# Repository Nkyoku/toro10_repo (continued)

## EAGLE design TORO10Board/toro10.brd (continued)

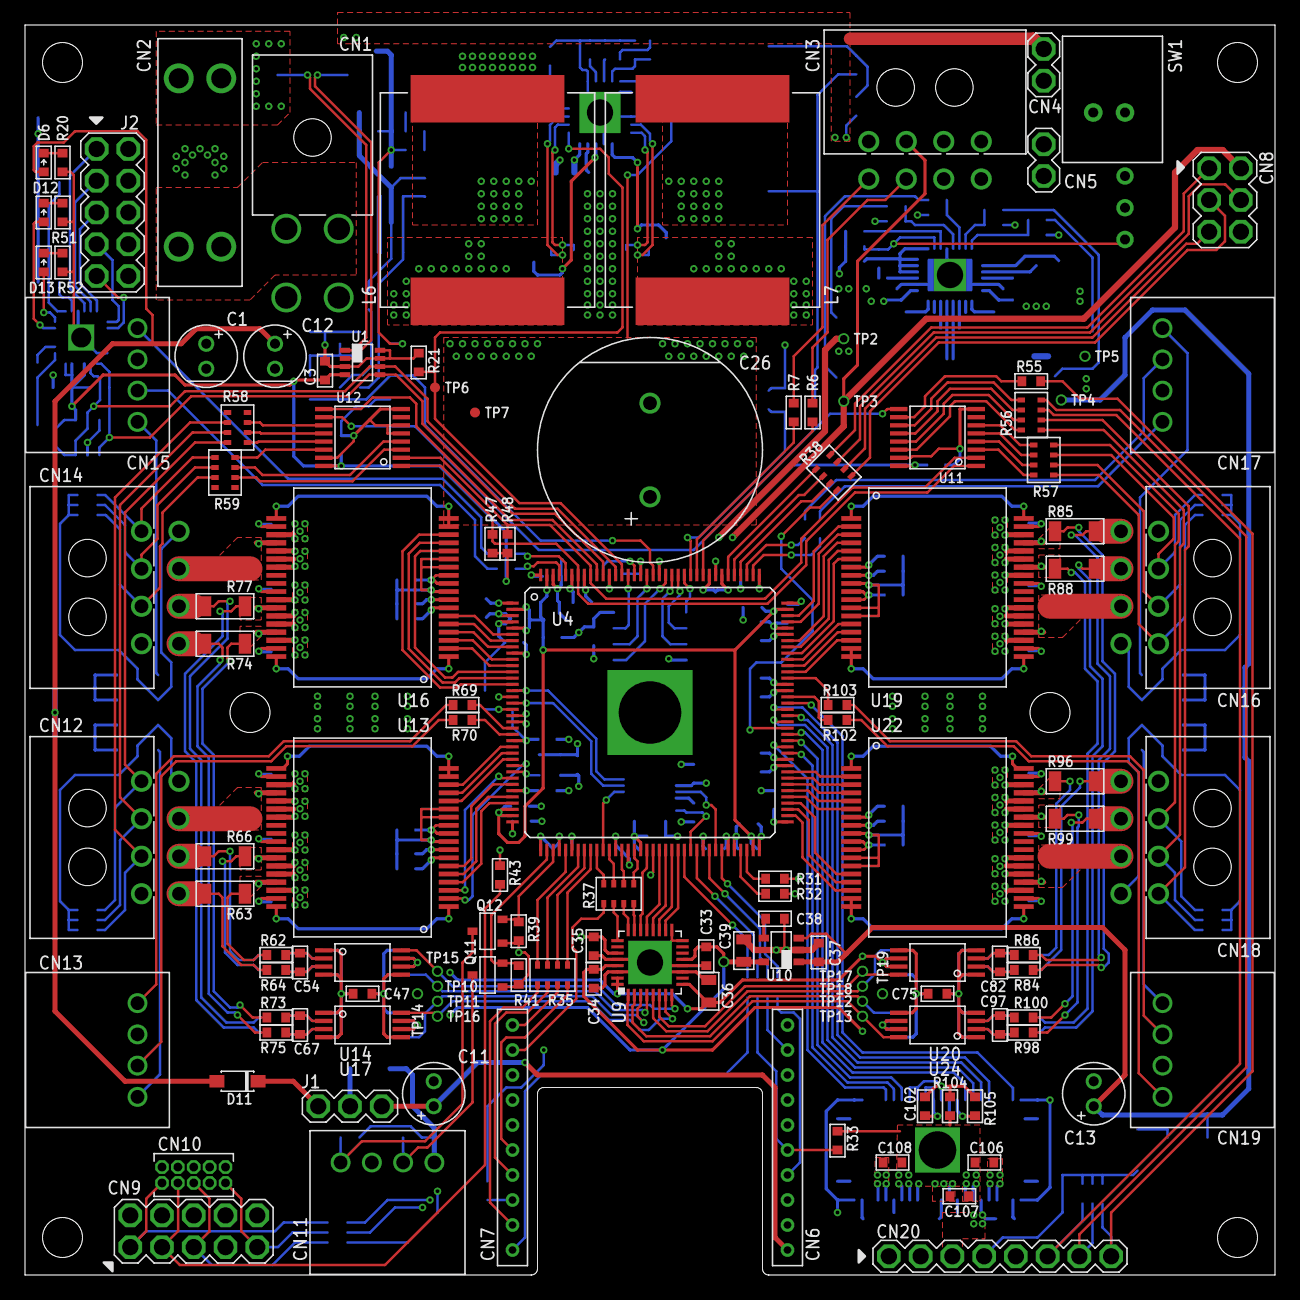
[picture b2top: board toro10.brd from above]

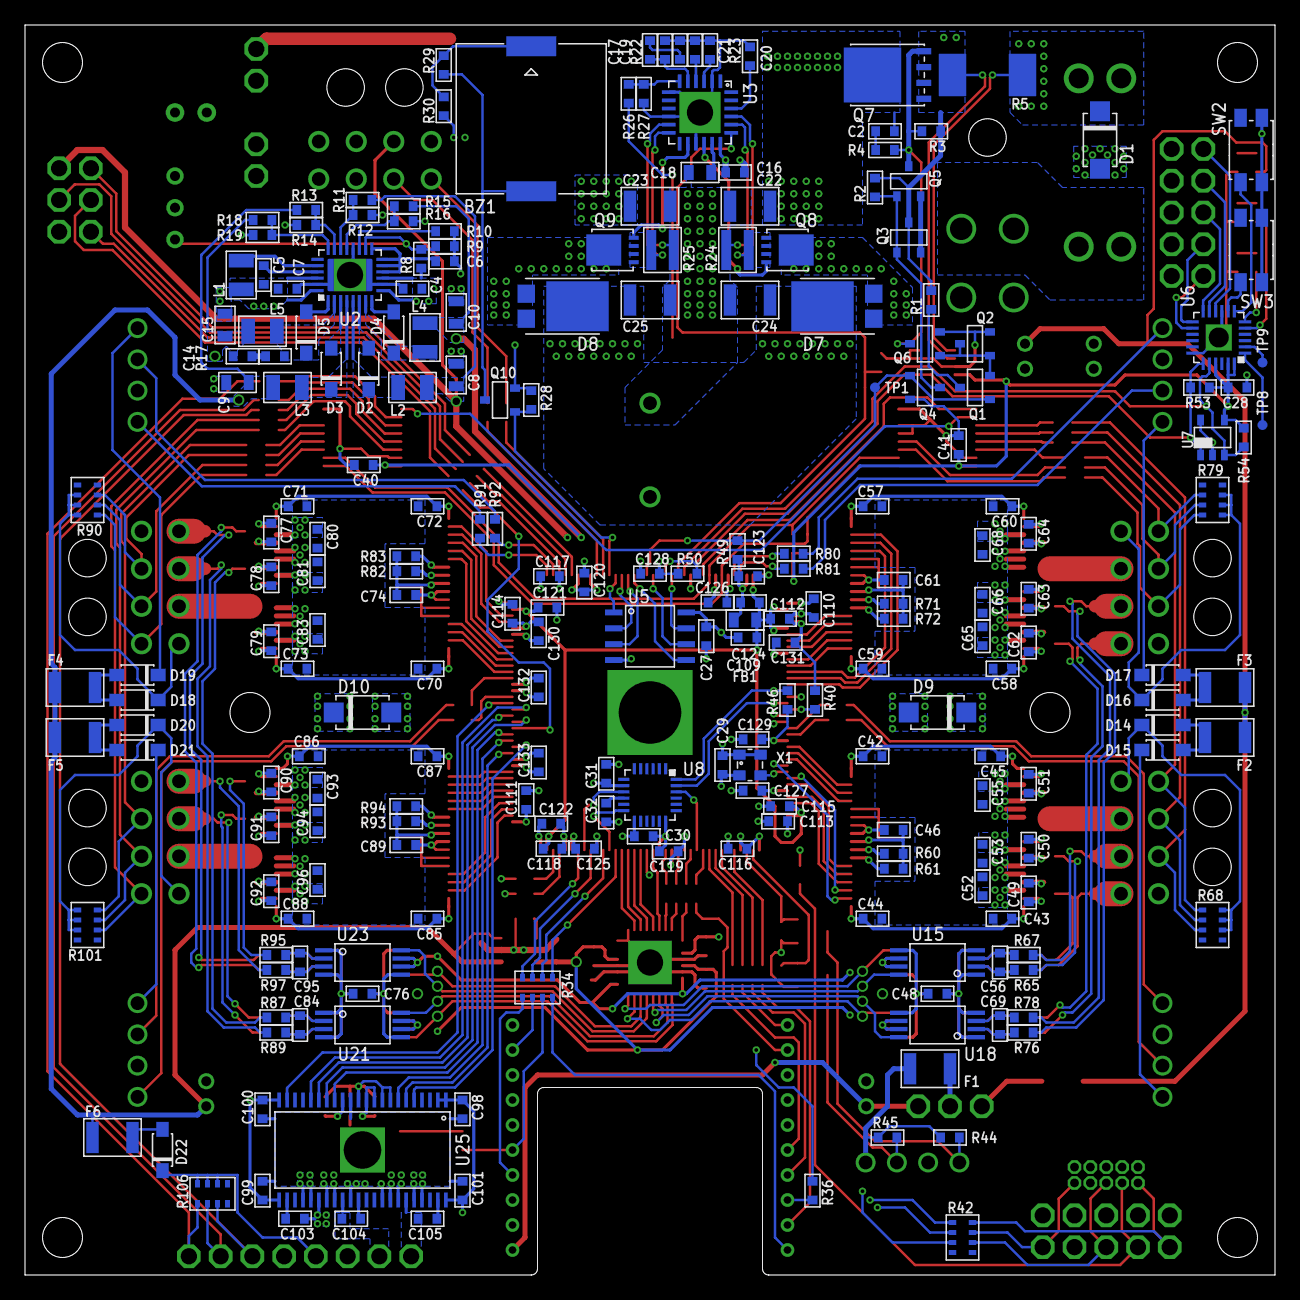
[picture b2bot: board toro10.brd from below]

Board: 4 copper layers, 100.0 x 100.0 mm, 358 parts (230 on the bottom side), 329 nets.

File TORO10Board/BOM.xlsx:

Device | Model Number | Value | Package | Qty | Parts
Resistor |  | 0Ω | 1608 | 16 | R62, R64, R65, R67, R73, R75, R76, R78, R84, R86, R87, R89, R95, R97, R98, R100
Resistor | WSLF25121L000FEA | 1mΩ | WSLF2512 | 1 | R5
Resistor |  | 2mΩ | 3216 | 8 | R63, R66, R74, R77, R85, R88, R96, R99
Resistor | PRL1632-R005-F-T1 | 5mΩ | 3216WL | 2 | R24, R25
Resistor |  | 1Ω | 1608 | 5 | R60, R71, R82, R93, R104
Resistor |  | 51Ω | 1608 | 6 | R6, R7, R31, R32, R36, R43
Resistor |  | 1kΩ | 1608 | 14 | R4, R17, R29, R30, R51, R52, R69, R70, R80, R81, R91, R92, R102, R103
Resistor |  | 2.2kΩ | 1608 | 7 | R21, R33, R44, R45, R49, R53, R54
Resistor |  | 3.3kΩ | 1608 | 1 | R19
Resistor |  | 4.7kΩ | 1608 | 5 | R20, R27, R28, R39, R41
Resistor |  | 10kΩ | 1608 | 8 | R2, R10, R40, R46, R47, R48, R50, R55
Resistor |  | 15kΩ | 1608 | 1 | R12
Resistor |  | 22kΩ | 1608 | 6 | R9, R14, R61, R72, R83, R94
Resistor |  | 33kΩ | 1608 | 1 | R23
Resistor |  | 47kΩ | 1608 | 4 | R11, R16, R18, R105
Resistor |  | 68.1kΩ | 1608 | 1 | R22
Resistor |  | 130kΩ | 1608 | 2 | R13, R15
Resistor |  | 180kΩ | 1608 | 1 | R26
Resistor |  | 220kΩ | 1608 | 2 | R1, R3
Resistor |  | 270kΩ | 1608 | 1 | R8
Resistor Array |  | 51Ωx4 | 3216 | 5 | R34, R35, R37, R38, R42
Resistor Array |  | 1kΩx4 | 3216 | 4 | R56, R57, R58, R59
Resistor Array |  | 100kΩx4 | 3216 | 5 | R68, R79, R90, R101, R106
Ceramic Capacitor |  | Do Not Mount | 1608 | 8 | C54, C56, C67, C69, C82, C84, C95, C97
Ceramic Capacitor |  | 100pF | 1608 | 1 | C19
Ceramic Capacitor |  | 1nF | 1608 | 2 | C14, C20
Ceramic Capacitor |  | 10nF | 1608 | 3 | C17, C29, C38
Ceramic Capacitor |  | 100nF 63V | 1608 | 72 | C2, C3, C6, C21, C27, C28, C31, C40, C41, C46, C47, C48, C49, C50, C51, C52, C5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
Ceramic Capacitor |  | 1uF 63V | 1608 | 30 | C4, C5, C7, C16, C30, C32, C33, C34, C35, C37, C42, C43, C44, C45, C57, C58, C5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
Ceramic Capacitor | GRM21BB31E106KA | 10uF 16V | 2012 | 7 | C8, ,C9, C10, C15, C18, C39, C109
Ceramic Capacitor | GRM32ER7YA106KA12 | 10uF 35V | 3225 | 2 | C22, C23
Ceramic Capacitor | GRM32ER71J106MA12L | 10uF 63V | 3225 | 2 | C24, C25
Ceramic Capacitor | GRM21BR61E226ME44 | 22uF 6.3V | 2012 | 1 | C36
Aluminum Capacitor | 35PK47MEFC5X11 | 47uF 35V | φ5mm | 1 | C1
Aluminum Capacitor | 25PK100MEFC5X11 | 100uF 16V | φ5mm | 3 | C11, C12, C13
Aluminum Capacitor | UPW1J391MHD6 | 390uF 63V | φ18mm | 1 | C26
Inductor | MAMK2520T4R7M | 4.7uH | 2520 | 5 | L1, L2, L3, L4, L5
Inductor | IHLP6767GZER8R2M11 | 8.2uH | 17.15mm x 17.15mm | 2 | L6, L7
Ferrite Bead | BLM18PG471SN1D |  | 1608 | 1 | FB1
Polyswitch | MICROSMD010F-02 |  | 3225 | 6 | F1, F2, F3, F4, F5, F6
Silicon Diode | GS1010FL |  | SOD123 | 10 | D11, D14, D15, D16, D17, D18, D19, D20, D21, D22
Schottky Diode | SS2040FL |  | SOD123 | 4 | D2, D3, D4, D5
Schottky Diode | FSV2060L |  | TO-277-3 | 2 | D7, D8
TVS Diode | SMAJ26A |  | DO-214AC | 1 | D1
TVS Diode | SMAJ48A |  | DO-214AC | 2 | D9, D10
LED |  | Green | 1608 | 1 | D12
LED |  | Orange | 1608 | 1 | D6
LED |  | Red | 1608 | 1 | D13
NPN Transistor | 2SC2712-GR |  | SOT23-3 | 2 | Q2, Q6
Nch MOSFET | BSS138 |  | SOT23-3 | 7 | Q1, Q3, Q4, Q5, Q10, Q11, Q12
Nch MOSFET | TPN7R506NH,L1Q |  | TSON-8_3.3 | 2 | Q8, Q9
Pch MOSFET | SI7135DP-T1-GE3 |  | POWERPAK-SO-8-S | 1 | Q7
LDO Regulator | SPX3819M5-L-5-0/TR |  | SOT23-5 | 1 | U10
Buck Regulator | LT3504EUFD#PBF |  | QFN28-0.5 | 1 | U2
Boost Regulator | LTC3862EUH-1#PBF |  | QFN24-0.65 | 1 | U3
Serializer | SN74LV165APWRG3 |  | TSSOP16 | 2 | U11, U12
A/D Conveter | ADS7223SRHBT |  | QFN32-0.5 | 1 | U9
Oscillator | ASDMB-30.000MHZ-LC-T |  | 2520 | 1 | X1
EEPROM | 24AA02E48T-I/OT |  | SOT23-5 | 1 | U7
Flash Memory | IS25LP016D-JNLE |  | SOP8 | 1 | U5
I/O Expander | PCAL6416AHF,128 |  | QFN24-0.5 | 1 | U6
Motor Driver | DRV8312DDWR |  | HTSSOP44 | 1 | U25
Motor Driver | DRV8332DKDR |  | HSSOP36 | 4 | U13, U16, U19, U22
Inertial Measurement Unit | ICM-20689 |  | QFN24 | 1 | U8
Current Sense Amplifier | INA219AIDCNR |  | SOT23-8 | 1 | U1
Current Sense Amplifier | INA240A2PWR |  | TSSOP8 | 8 | U14, U15, U17, U18, U20, U21, U23, U24
FPGA | 10M16SCE144C8G |  | QFP144 | 1 | U4
Piezoelectric Sounder | PKLCS1212E4001-R1 |  | PKLCS1212 | 1 | BZ1
Toggle Switch | B-12JV |  | B-12JV | 1 | SW1
Tactile Switch | EVQ-PUB02K |  | EVQ-PU_BK | 2 | SW2, SW3
Header | 3557-20 |  | 3557 | 1 | CN2
Header | 0430450801 |  | 43045-0800 | 5 | CN3, CN12, CN14, CN16, CN18
Header | 0534260410 |  | 53426-04 | 5 | CN11, CN13, CN15, CN17, CN19
Header | 0039301040 |  | 5569-04A2 | 1 | CN1
Pin Header | Pin Header 1x2 2.54mm Pitch |  | PIN1X2 | 2 | CN4, CN5
Pin Header | Pin Header 1x3 2.54mm Pitch |  | PIN1X3 | 1 | J1
Pin Header | Pin Header 1x8 2.54mm Pitch |  | PIN1X8 | 1 | CN20
Pin Header | Pin Header 2x3 2.54mm Pitch |  | PIN2X3 | 1 | CN8
Pin Header | Pin Header 2x5 1.27mm Pitch |  | PIN2X5-TH1.27 | 1 | CN10
Pin Header | Pin Header 2x5 2.54mm Pitch |  | PIN2X5 | 1 | CN9, J2
Pin Socket | 2209S-10G |  | SOCKET1X10-TH2.0 | 2 | CN6, CN7

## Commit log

2017-05-19 Add circuit
2017-05-20 Add libraries
2017-08-24 add kicker board
2017-08-24 move library
2017-08-24 add kicker BOM
